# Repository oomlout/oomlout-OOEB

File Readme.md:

# OOEB -- Oopen Electronic Blocks
## What OOEB Is

## The Wire

* Pin 1 -- Ground
* Pin 2 -- Vcc
* Pin 3 -- Signal
* Pin 4 -- Blank/blocked (for polarization)

## The Modules
### Outputs
#### OOEB-OUTP-LED-X -- Single LED
A single LED

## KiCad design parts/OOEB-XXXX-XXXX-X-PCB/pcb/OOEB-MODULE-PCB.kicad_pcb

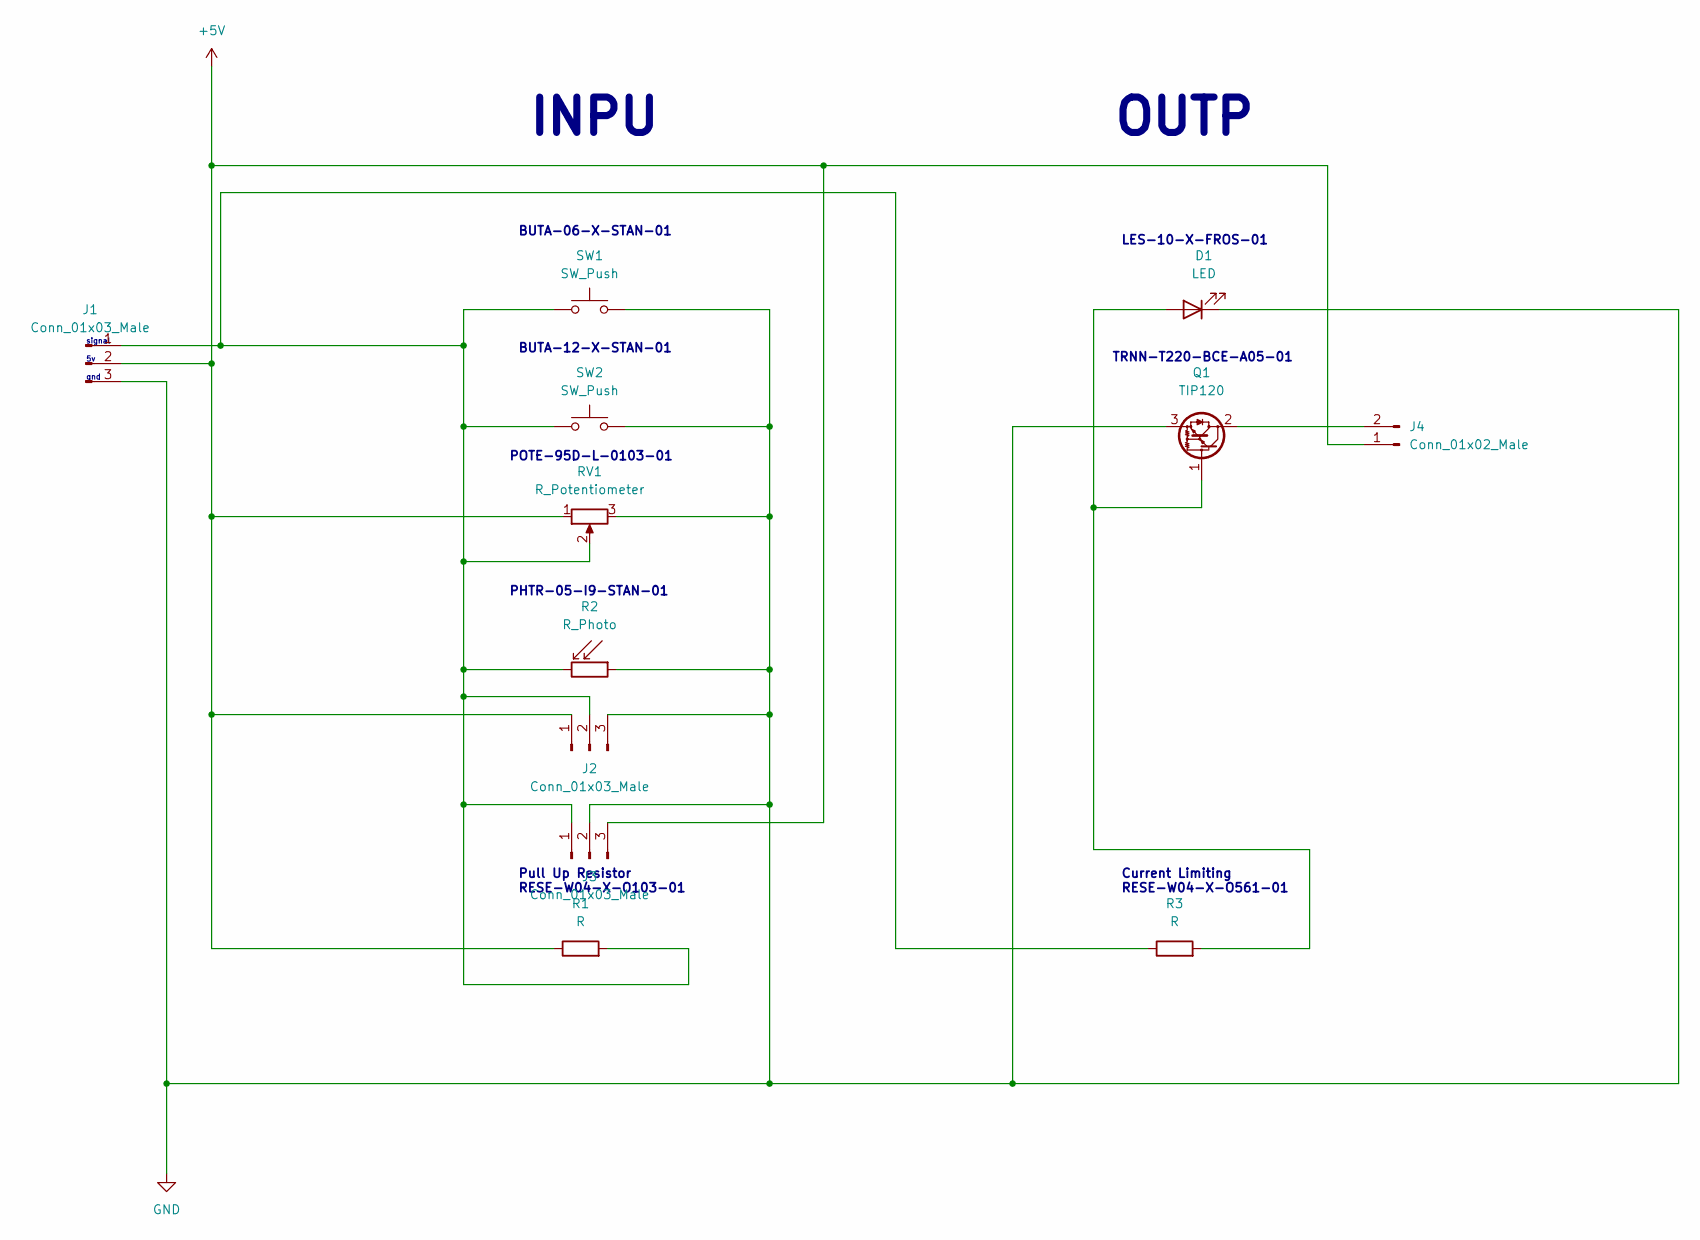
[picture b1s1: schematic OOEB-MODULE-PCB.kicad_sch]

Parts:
D1: LED; LED_D10.0mm
J1: Conn_01x03_Male; PinHeader_1x03_P2.54mm_Horizontal
J2, J3: Conn_01x03_Male; PinHeader_1x03_P2.54mm_Vertical
J4: Conn_01x02_Male; PinHeader_1x02_P2.54mm_Vertical
Q1: TIP120; TO-220-3_Vertical
R1, R3: R; R_Axial_DIN0411_L9.9mm_D3.6mm_P12.70mm_Horizontal
R2: R_Photo; R_LDR_10x8.5mm_P7.6mm_Vertical
RV1: R_Potentiometer
SW1: SW_Push; SW_PUSH_6mm
SW2: SW_Push; SW_PUSH-12mm

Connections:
+5V: J1.2, J2.1, J3.3, J4.1, R1.1, RV1.1
GND: D1.1 (K), J1.3, J2.3, J3.2, Q1.3 (E), R2.1, RV1.3, SW1.2, SW2.2
unnamed: D1.2 (A), Q1.1 (B), R3.2
unnamed: J1.1, J2.2, J3.1, R1.2, R2.2, R3.1, RV1.2, SW1.1, SW2.1
unnamed: J4.2, Q1.2 (C)

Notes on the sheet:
TRNN-T220-BCE-A05-01
POTE-95D-L-0103-01
LES-10-X-FROS-01
BUTA-12-X-STAN-01
OUTP
Pull Up Resistor RESE-W04-X-O103-01
BUTA-06-X-STAN-01
gnd
PHTR-05-I9-STAN-01
INPU
Current Limiting RESE-W04-X-O561-01
signal

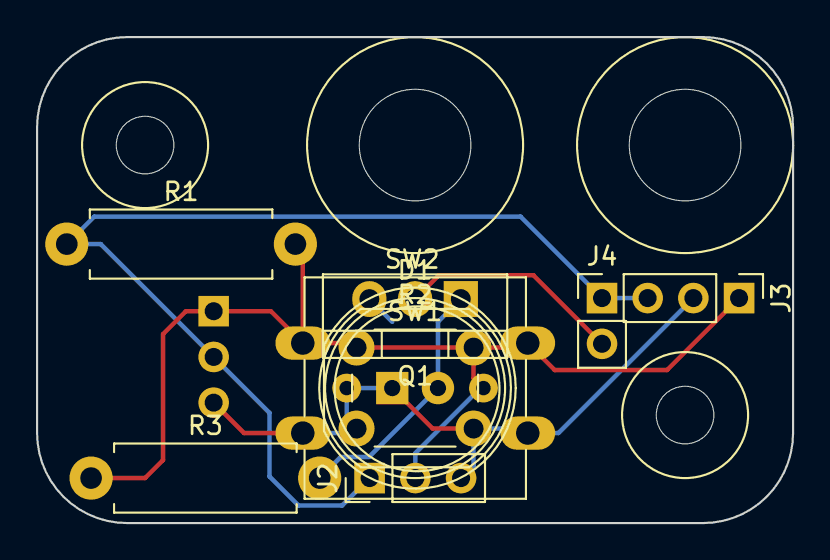
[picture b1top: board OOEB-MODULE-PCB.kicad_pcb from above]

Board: 2 copper layers, 42.0 x 27.0 mm, 11 parts (1 on the bottom side), 5 nets.

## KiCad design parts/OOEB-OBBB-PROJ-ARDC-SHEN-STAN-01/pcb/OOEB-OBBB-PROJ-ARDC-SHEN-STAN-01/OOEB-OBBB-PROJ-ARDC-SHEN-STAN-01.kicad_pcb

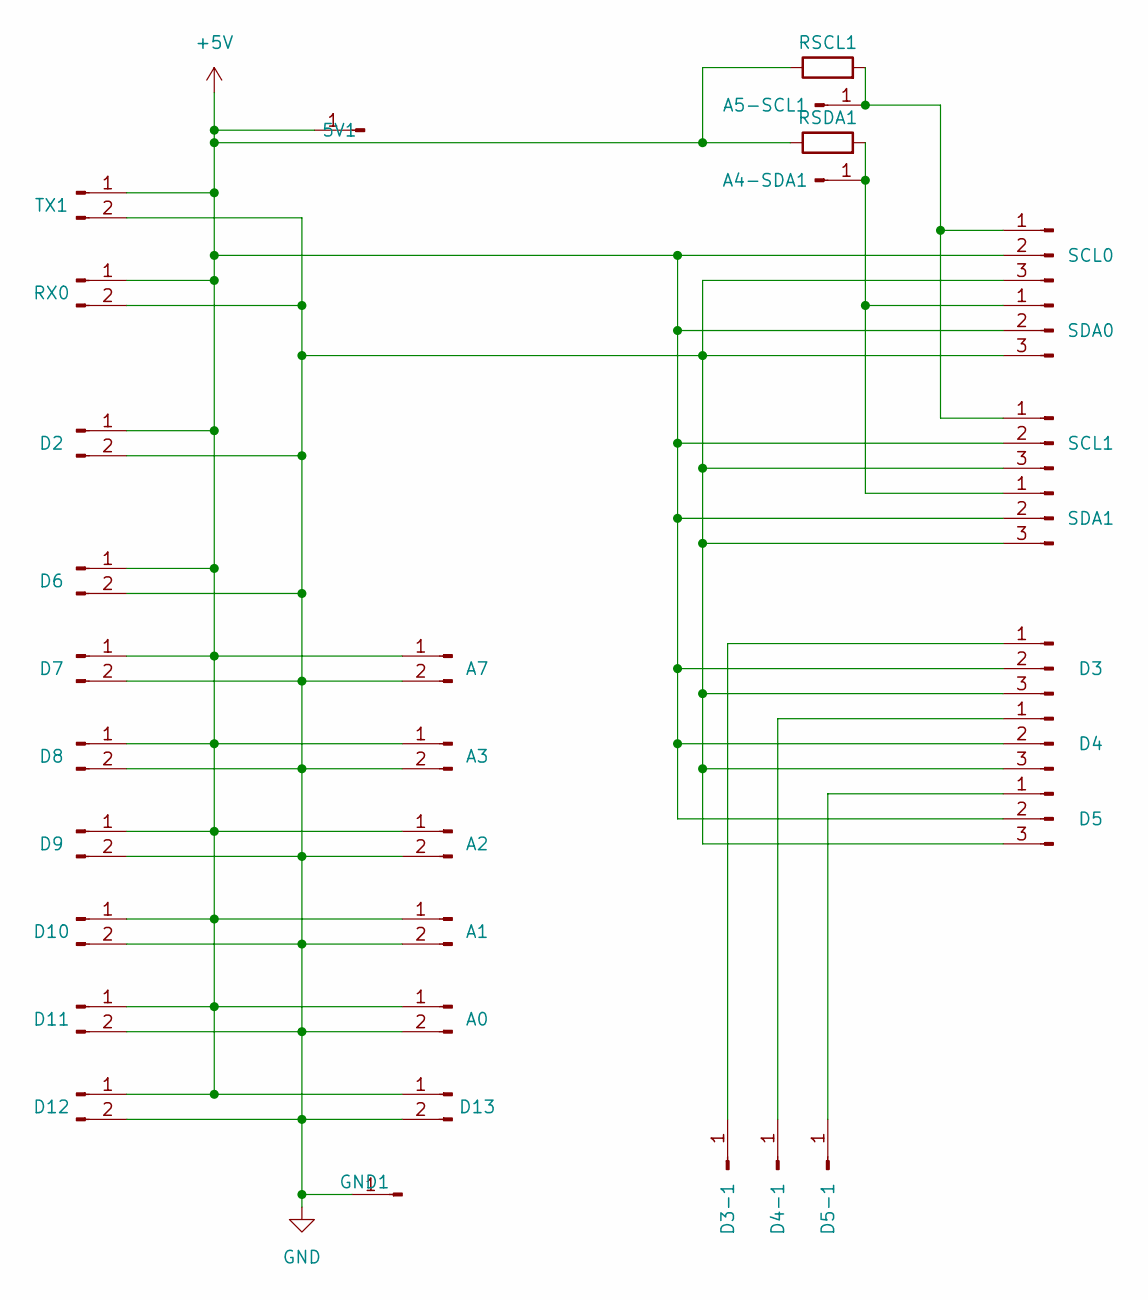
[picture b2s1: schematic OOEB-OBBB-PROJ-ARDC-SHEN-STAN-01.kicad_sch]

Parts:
5V1: Conn_01x01_Male; PinHeader_1x01_P2.54mm_Vertical
A0, A1, A2, A3, A7: Conn_01x02_Male; PinHeader_1x02_P2.54mm_Vertical
A4-SDA1, A5-SCL1: Conn_01x01_Male; PinHeader_1x01_P2.54mm_Vertical
D2, D6, D7, D8, D9, D10, D11, D12, D13: Conn_01x02_Male; PinHeader_1x02_P2.54mm_Vertical
D3, D4, D5: Conn_01x03_Male; PinHeader_1x03_P2.54mm_Vertical
D3-1, D4-1, D5-1: Conn_01x01_Male; PinHeader_1x01_P2.54mm_Vertical
GND1: Conn_01x01_Male; PinHeader_1x01_P2.54mm_Vertical
RSCL1: R; R_Axial_DIN0207_L6.3mm_D2.5mm_P7.62mm_Horizontal
RSDA1: R; R_Axial_DIN0207_L6.3mm_D2.5mm_P7.62mm_Horizontal
RX0: Conn_01x02_Male; PinHeader_1x02_P2.54mm_Vertical
SCL0, SCL1: Conn_01x03_Male; PinHeader_1x03_P2.54mm_Vertical
SDA0, SDA1: Conn_01x03_Male; PinHeader_1x03_P2.54mm_Vertical
TX1: Conn_01x02_Male; PinHeader_1x02_P2.54mm_Vertical

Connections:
+5V: 5V1.1, A0.1, A1.1, A2.1, A3.1, A7.1, D2.1, D3.2, D4.2, D5.2, D6.1, D7.1, D8.1, D9.1, D10.1, D11.1, D12.1, D13.1, RSCL1.1, RSDA1.1, RX0.1, SCL0.2, SCL1.2, SDA0.2, SDA1.2, TX1.1; also elsewhere on the board
GND: A0.2, A1.2, A2.2, A3.2, A7.2, D2.2, D3.3, D4.3, D5.3, D6.2, D7.2, D8.2, D9.2, D10.2, D11.2, D12.2, D13.2, GND1.1, RX0.2, SCL0.3, SCL1.3, SDA0.3, SDA1.3, TX1.2; also elsewhere on the board
unnamed: A4-SDA1.1, RSDA1.2, SDA0.1, SDA1.1
unnamed 3: A5-SCL1.1, RSCL1.2, SCL0.1, SCL1.1; also elsewhere on the board
unnamed: D3.1, D3-1.1
unnamed: D4.1, D4-1.1
unnamed: D5.1, D5-1.1

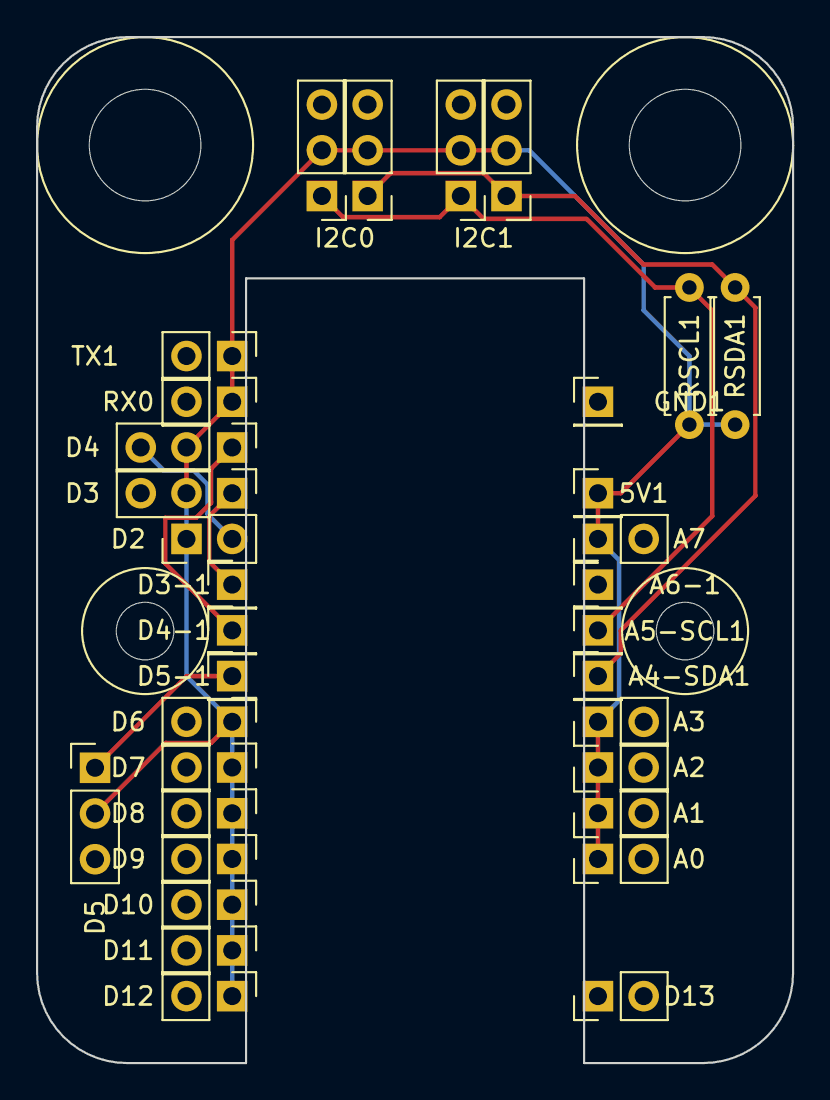
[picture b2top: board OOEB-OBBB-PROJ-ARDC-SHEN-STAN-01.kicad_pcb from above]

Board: 2 copper layers, 42.0 x 57.0 mm, 33 parts (0 on the bottom side), 7 nets.

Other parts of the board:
A6-1: Conn_01x01_Male; PinHeader_1x01_P2.54mm_Vertical
I2C0, I2C1: Conn_01x03_Male; PinHeader_1x03_P2.54mm_Vertical

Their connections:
+5V: I2C0.2, I2C1.2; also elsewhere on the board
GND: I2C0.3, I2C1.3; also elsewhere on the board
unnamed 3: I2C0.1, I2C1.1; also elsewhere on the board

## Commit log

2018-10-11 :lollipop: Added .gitattributes & .gitignore files
2018-10-11 Initial Transfer from OOBB to OOEB (building blocks to electronic blocks)
2018-10-11 Added a breadboard (14-10 A4)
2018-10-11 Added the HL directory from OOBB ((needs splitting between MO and WI))
2018-10-17 Worked on components a bit.
2018-10-17 Made CO's for 4.5mm springs.
2018-10-19 Added a new style of component holder Working-CO
2019-02-17 Added resistor to arcade button OOEB.
2019-02-26 Removed servo holders.
2019-02-26 Added a wiring diagram.
2019-04-12 Changed wiring guide from OOBB to OOEB
2019-04-12 Added connector footprints
2019-05-08 Added WI-EX for 2 signals and high voltage on one plug.
2019-05-08 Added extra box and changed a wire.
2019-05-17 Worked on OOED-EX wiring standard.
2019-05-18 Fixed up footprints.
2019-10-14 Worked on an HL for an FSR.
2019-10-20 Worked a bit.
2022-05-30 Big Change
2022-06-02 Loads of progress.
2022-06-02 First run at a python wrapper.
2022-06-05 First refactoring.
2022-06-05 Added python to gitignore.
2022-06-05 Major works.
2022-06-05 Generated everything.
2022-06-15 Worked on PCB bases.
2022-09-30 Minor works
